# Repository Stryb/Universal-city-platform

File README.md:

# Universal-city-platform
робот для уборки городских територий

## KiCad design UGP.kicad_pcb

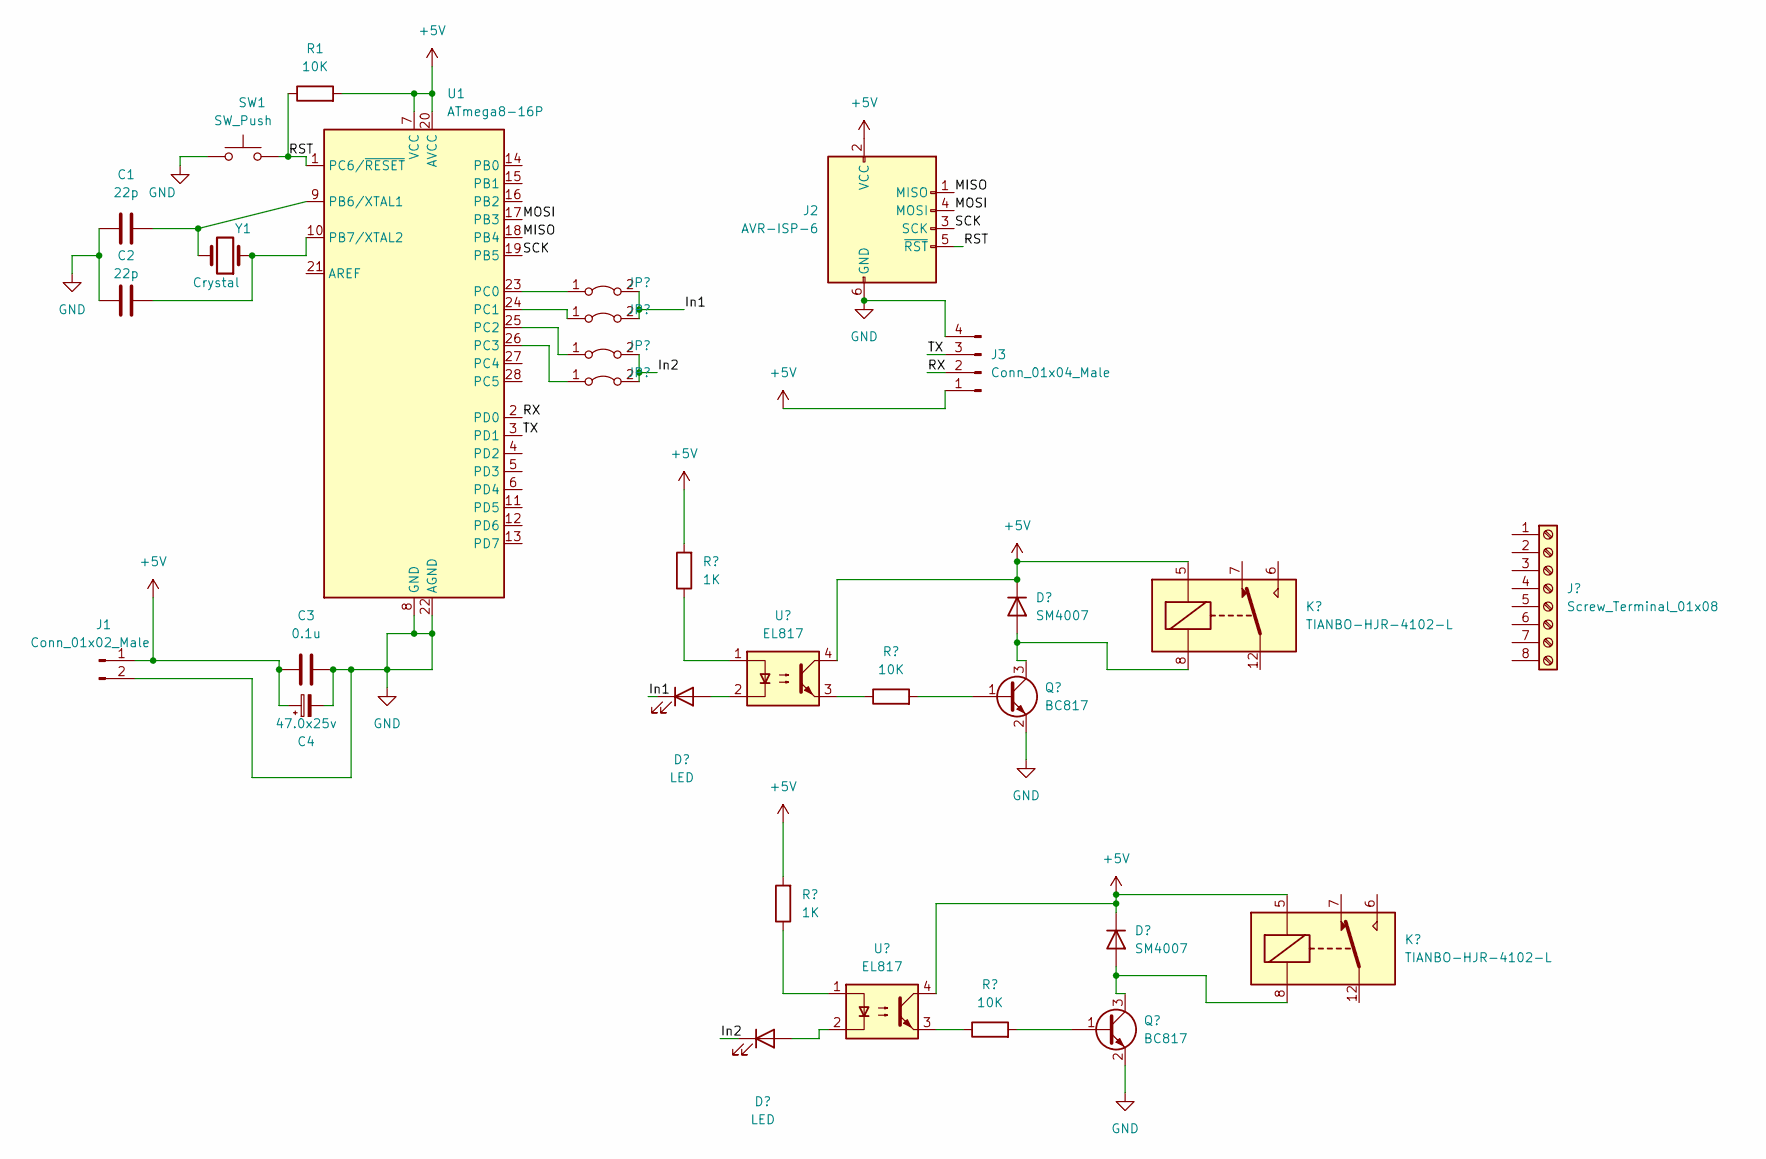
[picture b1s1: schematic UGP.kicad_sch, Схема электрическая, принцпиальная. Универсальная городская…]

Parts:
C1, C2: 22p; C_0805_2012Metric
C3: 0.1u; C_0805_2012Metric
C4: 47.0x25v; CP_Elec_6.3x5.4
J1: Conn_01x02_Male; PinHeader_1x02_P2.54mm_Vertical
J2: AVR-ISP-6; IDC-Header_2x03_P2.54mm_Vertical
J3: Conn_01x04_Male; JST_EH_B4B-EH-A_1x04_P2.50mm_Vertical
R1: 10K; R_0805_2012Metric
SW1: SW_Push; SW_Push_SPST_NO_Alps_SKRK
U1: ATmega8-16P; DIP-28_W7.62mm
Y1: Crystal; Crystal_HC49-4H_Vertical

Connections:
+5V: C3.1, C4.1, J1.1, J2.2 (VCC), J3.1, R1.2, U1.7 (VCC), U1.20 (AVCC)
/MISO: J2.1 (MISO), U1.18 (PB4)
/MOSI: J2.4 (MOSI), U1.17 (PB3)
/RST: J2.5 (~RST), R1.1, SW1.2, U1.1 (PC6/~RESET)
/RX: J3.2, U1.2 (PD0)
/SCK: J2.3 (SCK), U1.19 (PB5)
/TX: J3.3, U1.3 (PD1)
GND: C1.1, C2.1, C3.2, C4.2, J1.2, J2.6 (GND), J3.4, SW1.1, U1.8 (GND), U1.22 (AGND)
unnamed: C1.2, U1.9 (PB6/XTAL1), Y1.2
unnamed: C2.2, U1.10 (PB7/XTAL2), Y1.1

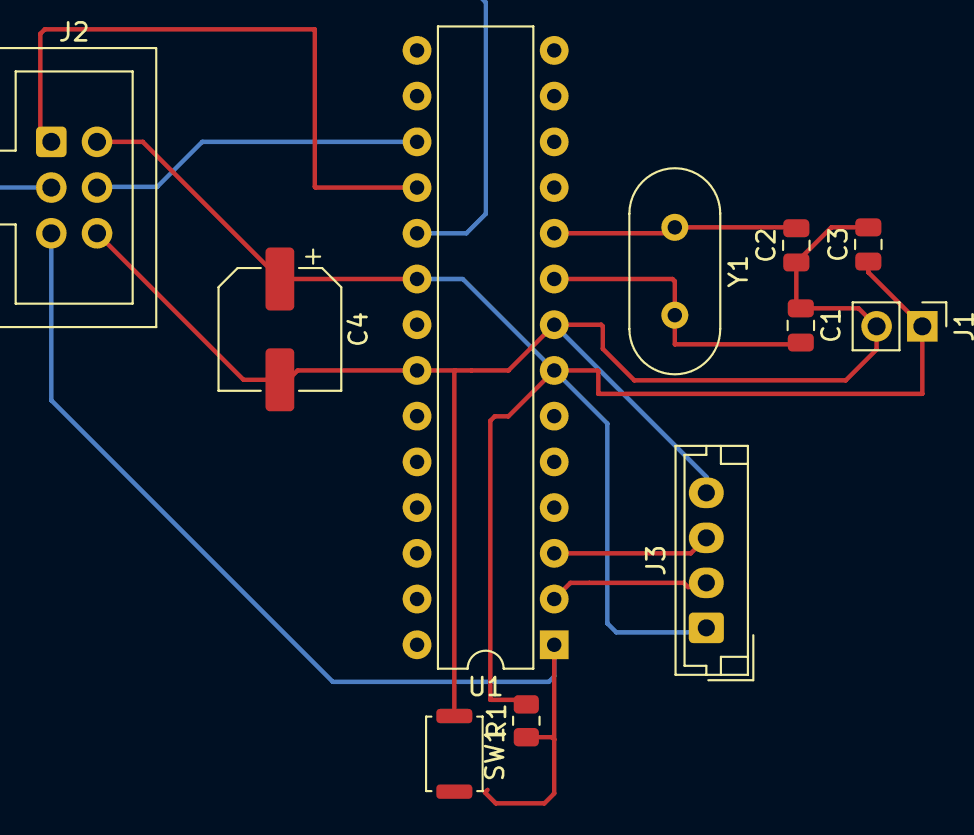
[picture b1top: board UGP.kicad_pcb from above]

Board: 2 copper layers, 11 parts (0 on the bottom side), 10 nets.

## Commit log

2022-11-13 kicad файлы
